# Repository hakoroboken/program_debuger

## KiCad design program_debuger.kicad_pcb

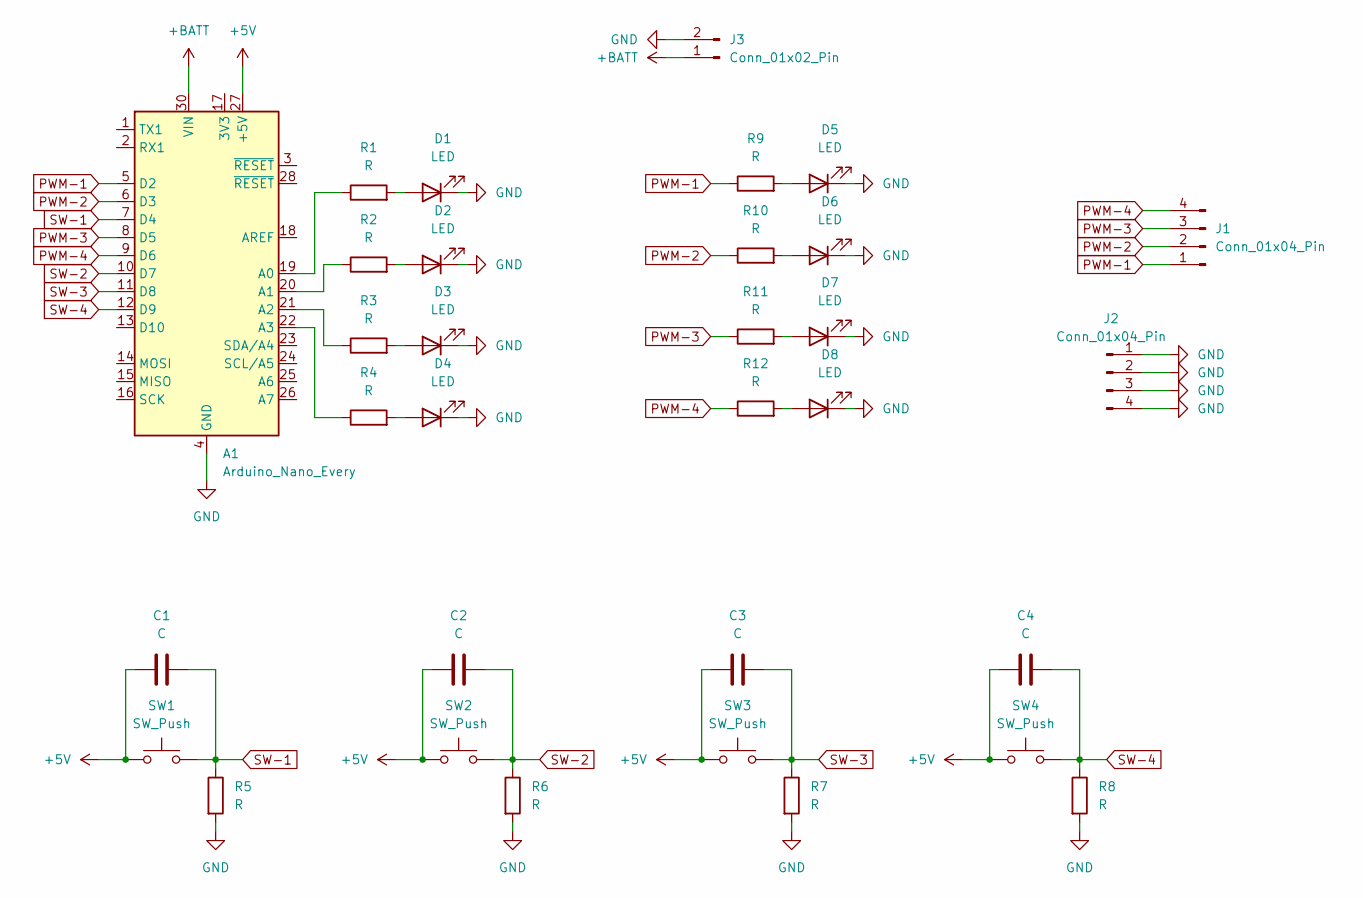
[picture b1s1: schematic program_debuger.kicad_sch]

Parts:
A1: Arduino_Nano_Every; Arduino_Nano
C1, C2, C3, C4: C; C_Disc_D6.0mm_W4.4mm_P5.00mm
D1, D2, D3, D4, D5, D6, D7, D8: LED; LED_D3.0mm
J1, J2: Conn_01x04_Pin; PinHeader_1x04_P2.54mm_Vertical
J3: Conn_01x02_Pin; AMASS_XT60-M_1x02_P7.20mm_Vertical
R1, R2, R3, R4, R5, R6, R7, R8, R9, R10, R11, R12: R; R_Axial_DIN0207_L6.3mm_D2.5mm_P10.16mm_Horizontal
SW1, SW2, SW3, SW4: SW_Push; SW_PUSH_6mm

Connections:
+5V: A1.27 (+5V), C1.1, C2.1, C3.1, C4.1, SW1.1, SW2.1, SW3.1, SW4.1
+BATT: A1.30 (VIN), J3.1
GND: A1.4 (GND), A1.29 (GND), D1.1 (K), D2.1 (K), D3.1 (K), D4.1 (K), D5.1 (K), D6.1 (K), D7.1 (K), D8.1 (K), J2.1, J2.2, J2.3, J2.4, J3.2, R5.2, R6.2, R7.2, R8.2
unnamed: A1.19 (A0), R1.1
unnamed: A1.20 (A1), R2.1
unnamed: A1.21 (A2), R3.1
unnamed: A1.22 (A3), R4.1
unnamed: D1.2 (A), R1.2
unnamed: D2.2 (A), R2.2
unnamed: D3.2 (A), R3.2
unnamed: D4.2 (A), R4.2
unnamed: D5.2 (A), R9.2
unnamed: D6.2 (A), R10.2
unnamed: D7.2 (A), R11.2
unnamed: D8.2 (A), R12.2
PWM-1: A1.5 (D2), J1.1, R9.1
PWM-2: A1.6 (D3), J1.2, R10.1
PWM-3: A1.8 (D5), J1.3, R11.1
PWM-4: A1.9 (D6), J1.4, R12.1
SW-1: A1.7 (D4), C1.2, R5.1, SW1.2
SW-2: A1.10 (D7), C2.2, R6.1, SW2.2
SW-3: A1.11 (D8), C3.2, R7.1, SW3.2
SW-4: A1.12 (D9), C4.2, R8.1, SW4.2

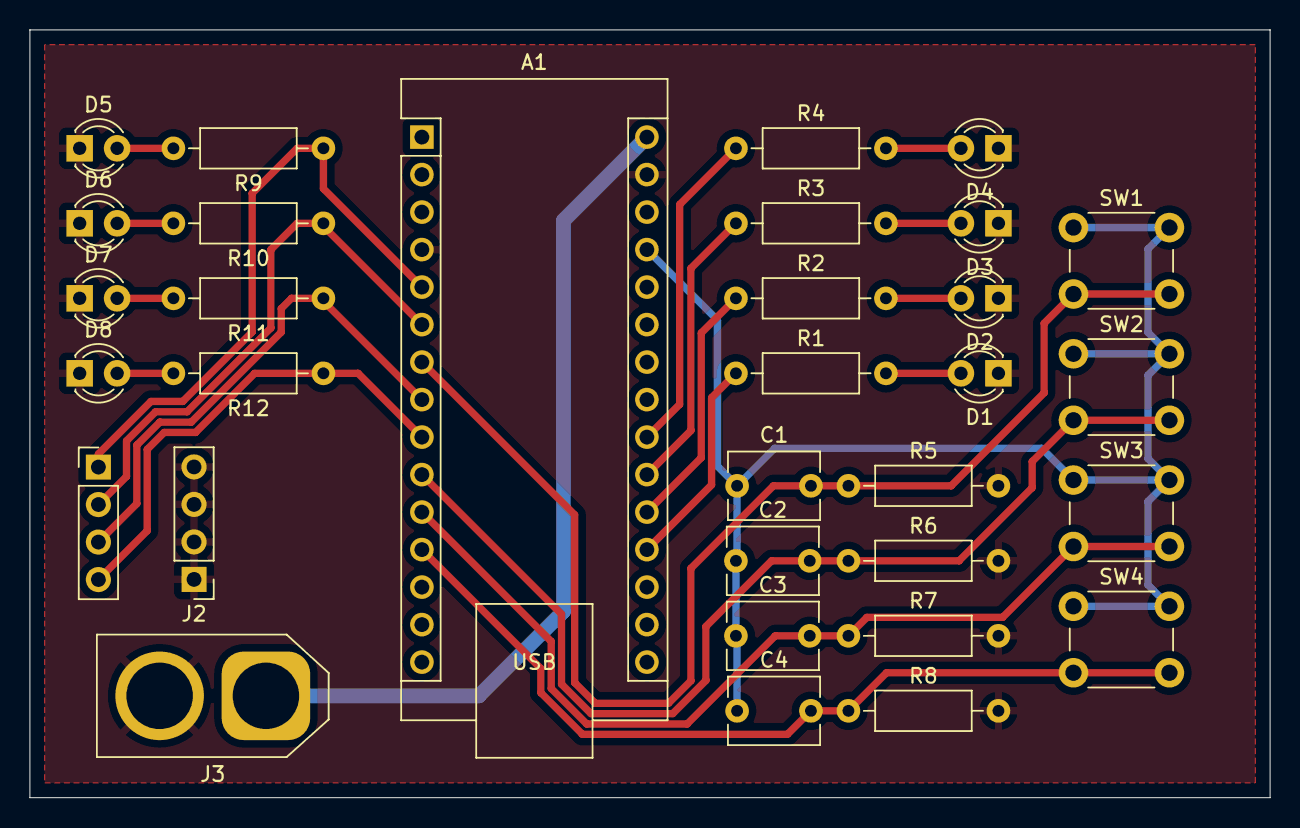
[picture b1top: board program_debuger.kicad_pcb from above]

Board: 2 copper layers, 84.0 x 52.0 mm, 32 parts (0 on the bottom side), 23 nets.

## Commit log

2024-05-05 init
